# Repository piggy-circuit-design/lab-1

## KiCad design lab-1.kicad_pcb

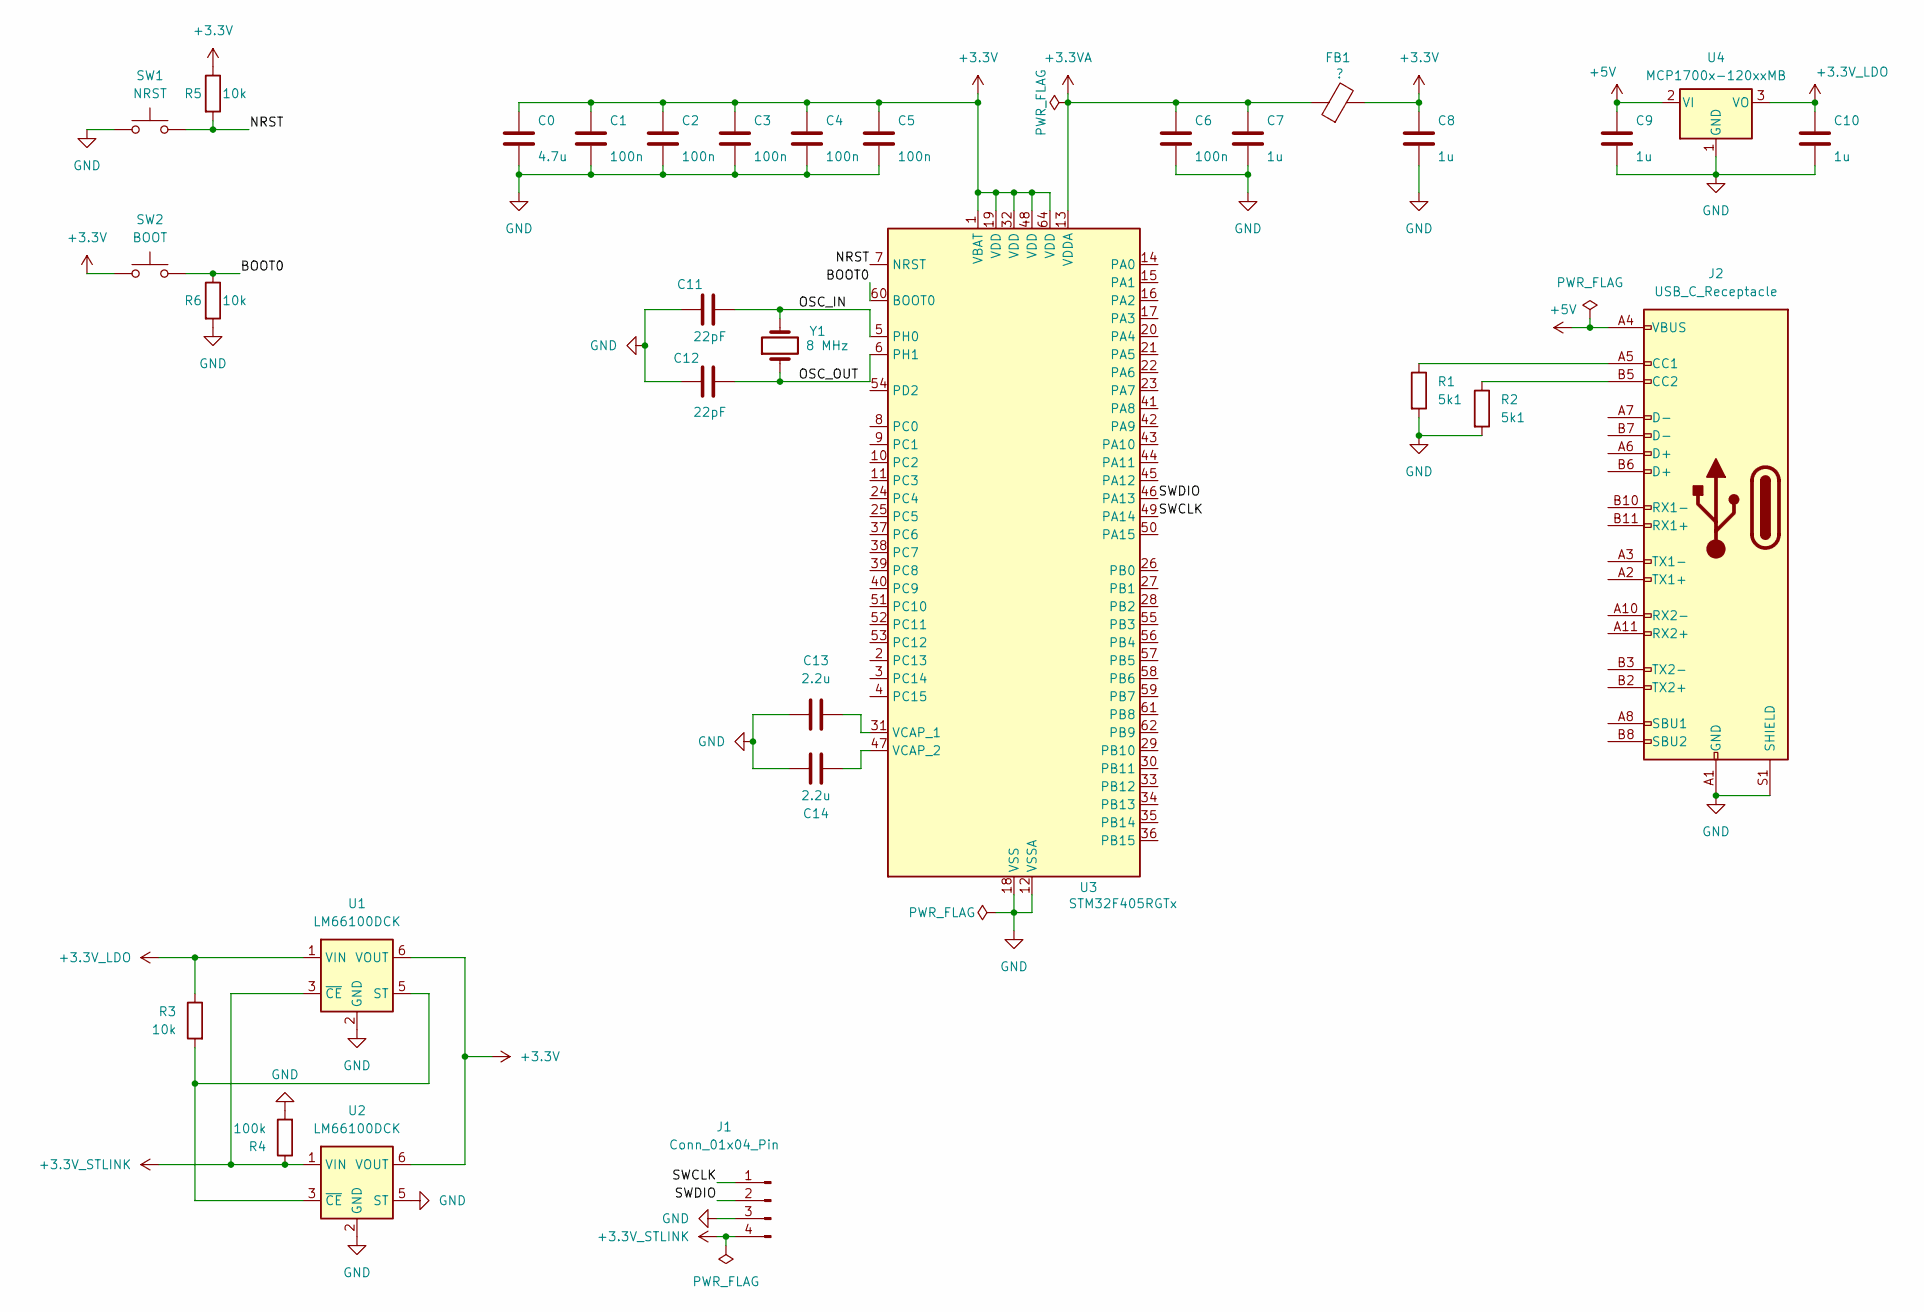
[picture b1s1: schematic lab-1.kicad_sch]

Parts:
C0: 4.7u; C_0603_1608Metric
C1, C2, C3, C4, C5, C6: 100n; C_0402_1005Metric
C7, C8, C9, C10: 1u; C_0603_1608Metric
C11, C12: 22pF; C_0402_1005Metric
C13, C14: 2.2u; C_0402_1005Metric
FB1: ?; L_0603_1608Metric
J1: Conn_01x04_Pin; PinHeader_1x04_P2.54mm_Vertical
J2: USB_C_Receptacle; USB_C_Receptacle_Amphenol_12401610E4-2A
R1, R2: 5k1; R_0603_1608Metric
R3: 10k; R_0603_1608Metric
R4: 100k; R_0603_1608Metric
R5, R6: 10k; R_0402_1005Metric
SW1: NRST; SW_PUSH_6mm_H4.3mm
SW2: BOOT; SW_PUSH_6mm_H4.3mm
U1, U2: LM66100DCK; SOT-363_SC-70-6
U3: STM32F405RGTx; LQFP-64_10x10mm_P0.5mm
U4: MCP1700x-120xxMB; SOT-89-3
Y1: 8 MHz; Crystal_SMD_2520-4Pin_2.5x2.0mm

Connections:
+3.3V: C0.1, C1.1, C2.1, C3.1, C4.1, C5.1, C8.1, FB1.2, R5.1, SW2.2, U1.6 (VOUT), U2.6 (VOUT), U3.1 (VBAT), U3.19 (VDD), U3.32 (VDD), U3.48 (VDD), U3.64 (VDD)
+3.3VA: C6.1, C7.1, FB1.1, U3.13 (VDDA)
+3.3V_LDO: C10.1, R3.1, U1.1 (VIN), U4.3 (VO)
+3.3V_STLINK: J1.4, R4.1, U1.3 (~CE), U2.1 (VIN)
+5V: C9.1, J2.A4 (VBUS), J2.A9 (VBUS), J2.B4 (VBUS), J2.B9 (VBUS), U4.2 (VI)
/BOOT0: R6.1, SW2.1, U3.60 (BOOT0)
/NRST: R5.2, SW1.1, U3.7 (NRST)
/OSC_IN: C11.2, U3.5 (PH0), Y1.2
/OSC_OUT: C12.2, U3.6 (PH1), Y1.1
/SWCLK: J1.1, U3.49 (PA14)
/SWDIO: J1.2, U3.46 (PA13)
GND: C0.2, C1.2, C2.2, C3.2, C4.2, C5.2, C6.2, C7.2, C8.2, C9.2, C10.2, C11.1, C12.1, C13.1, C14.2, J1.3, J2.A1 (GND), J2.A12 (GND), J2.B1 (GND), J2.B12 (GND), J2.S1 (SHIELD), R1.2, R2.2, R4.2, R6.2, SW1.2, U1.2 (GND), U2.2 (GND), U2.5 (ST), U3.12 (VSSA), U3.18 (VSS), U3.63 (VSS), U4.1 (GND)
unnamed: J2.A5 (CC1), R1.1
unnamed: J2.B5 (CC2), R2.1
unnamed: R3.2, U1.5 (ST), U2.3 (~CE)
unnamed: C13.2, U3.31 (VCAP_1)
unnamed: C14.1, U3.47 (VCAP_2)

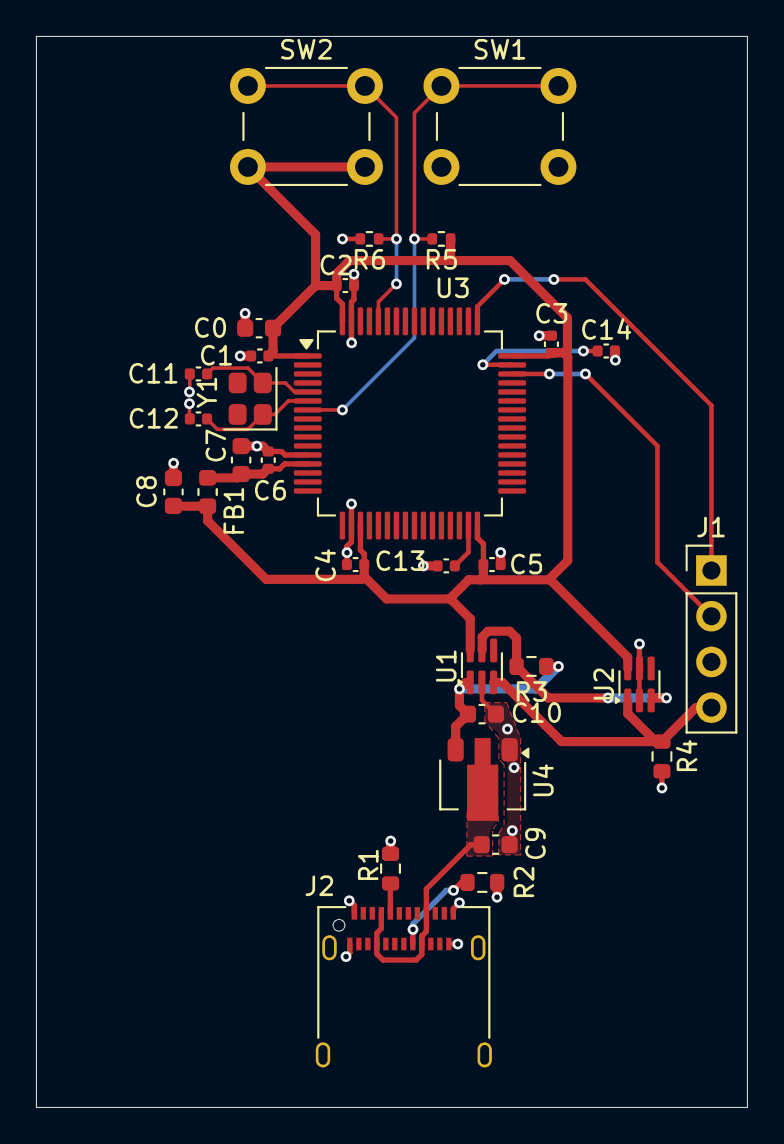
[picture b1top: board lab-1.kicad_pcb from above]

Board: 2 copper layers, 39.5 x 59.5 mm, 31 parts (0 on the bottom side), 17 nets.

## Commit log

2026-02-23 Added decoupling capacitors
2026-02-23 Changed the footprints + track width
2026-02-24 Modified tracks and capacitor placing Added type-c and LDO MCP1700 as source of power for STM
2026-03-05 add a programmer header and power ORing
2026-03-07 add crystal
2026-03-11 Added buttons
2026-03-17 add VCAP
2026-03-21 minor adjustments
